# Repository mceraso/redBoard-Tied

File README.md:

# redBoard-Tied
Eagle Project to tie together redundant pins of the Sparkfun Quadstepper Motor Driver Board (the Red Board). When UNO Robotics first used the Red Board,
we realized quickly that we did not need all the pins available on the board. We wanted to save space on our Arduino, so we began to solder connections as pictured below.
After Sparkfun retired the Red Board, we were interested to see that they had left their designs open to the public. We wondered if we could continue making our own Red Boards while iterating on their design.
This project attempted to tie together the pins on the board that we used to solder by hand.

The first prototype failed in spectacular fashion as pictured below. We ordered our Red Board design from MacroFab with 1oz copper while Sparkfun's original design demanded 2oz copper. Because our prototpye had half as much copper as it needed, it could not handle the current, heated up quickly, and caught fire.

UNO Robotics has decided to put this project on hold due to the high cost of 2oz copper board fabrication and because the University of New Orleans has acquired its own PCB fabrication machine. As we improve in-house PCB fabrication ability, we intend to come back to the RedBoard project.

8.29.18: DEVELOPMENT IS BACK ON.
Because of our performance in the 2018 season, UNO Robotics has secured funding to move forward with a prototype of redBoard-Tied with 2oz copper. We're finalzing the parts list and will place an order with MacroFab soon.

# Original Red Board Front: 

# Original Red Board Back:

# How We Used to Tie the Board:

# redBoard-Tied Front:

# redBoard-Tied Back:

# Prototype Front:

# Prototype Back:

# Helpful Links:
Quadstepper from SparkFun: https://www.sparkfun.com/products/retired/10507

Sparkfun's Quadstepper Repository: https://github.com/sparkfun/Quadstepper_Motor_Driver/tree/V_2.0.1

MacroFab: https://macrofab.com/

Eagle Tutorial from SparkFun: https://learn.sparkfun.com/tutorials/how-to-install-and-setup-eagle

UNO Robotics: http://www.uno.edu/student-involvement-leadership/orgs/robotics-club.aspx

GoFundMe: https://www.gofundme.com/unorobotics

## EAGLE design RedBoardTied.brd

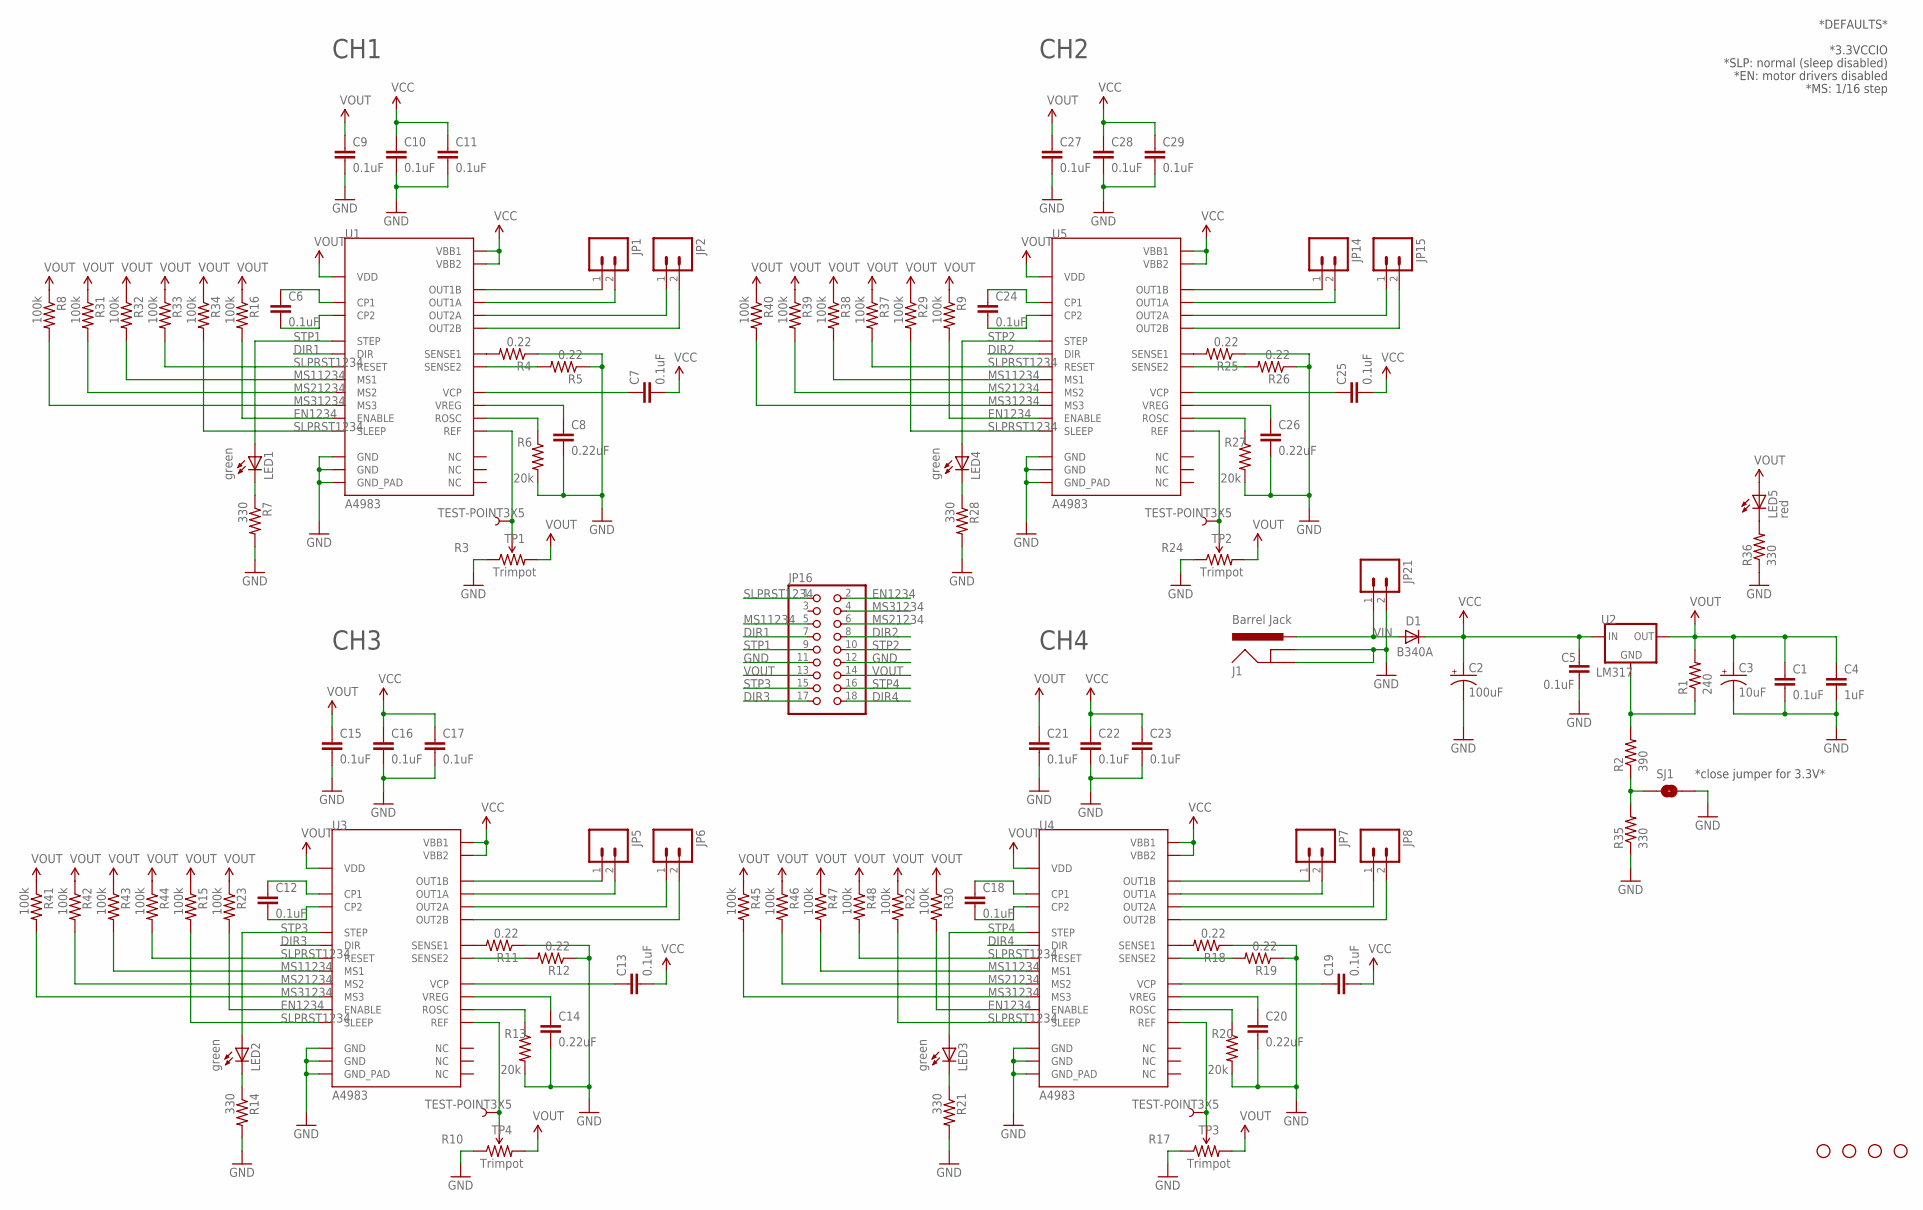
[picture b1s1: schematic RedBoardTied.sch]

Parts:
C1, C5, C6, C7, C9, C10, C11, C12, C13, C15, C16, C17, C18, C19, C21, C22, C23, C24, C25, C27, C28, C29: 0.1uF; 0402-CAP
C2: 100uF; PANASONIC_G
C3: 10uF; EIA3216
C4: 1uF; 0805
C8, C14, C20, C26: 0.22uF; 0402-CAP
D1: B340A; SMA-DIODE
J1: Barrel Jack; POWER_JACK_SMD
JP1, JP2, JP5, JP6, JP7, JP8, JP14, JP15: M023.5MM_LOCK; SCREWTERMINAL-3.5MM-2_LOCK
JP9, JP10, JP11, JP12: STAND-OFF
JP16: PINHD-2X9; 2X09
JP21: M02PTH; 1X02
LED1, LED2, LED3, LED4: green; LED-0603
LED5: red; LED-0603
R1: 240; 0402-RES
R2: 390; 0402-RES
R3, R10, R17, R24: Trimpot; TRIMPOT-3MM
R4, R5, R11, R12, R18, R19, R25, R26: 0.22; 0805
R6, R13, R20, R27: 20k; 0402-RES
R7, R14, R21, R28, R35, R36: 330; 0402-RES
R8, R9, R15, R16, R22, R23, R29, R30, R31, R32, R33, R34, R37, R38, R39, R40, R41, R42, R43, R44, R45, R46, R47, R48: 100k; 0402-RES
SJ1: SOLDERJUMPERNO; SJ_2S-NO
TP1, TP2, TP3, TP4: TEST-POINT3X5; PAD.03X.05
U1, U3, U4, U5: A4983; QFN-28-5MM
U2: LM317; DPAK

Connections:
DIR1: JP16.7, U1.P$19 (DIR)
DIR2: JP16.8, U5.P$19 (DIR)
DIR3: JP16.17, U3.P$19 (DIR)
DIR4: JP16.18, U4.P$19 (DIR)
EN1234: JP16.2, R9.2, R16.2, R23.2, R30.2, U1.P$2 (ENABLE), U3.P$2 (ENABLE), U4.P$2 (ENABLE), U5.P$2 (ENABLE)
GND: C1.2, C2.-, C3.C (-), C4.2, C5.2, C8.2, C9.2, C10.2, C11.2, C14.2, C15.2, C16.2, C17.2, C20.2, C21.2, C22.2, C23.2, C26.2, C27.2, C28.2, C29.2, J1.GND (GNDBREAK), J1.P$4 (GND), JP16.11, JP16.12, JP21.2, R3.1 (CCW), R4.1, R5.1, R6.2, R7.2, R10.1 (CCW), R11.1, R12.1, R13.2, R14.2, R17.1 (CCW), R18.1, R19.1, R20.2, R21.2, R24.1 (CCW), R25.1, R26.1, R27.2, R28.2, R35.1, R36.1, SJ1.2, U1.P$3 (GND), U1.P$18 (GND), U1.P$29 (GND_PAD), U3.P$3 (GND), U3.P$18 (GND), U3.P$29 (GND_PAD), U4.P$3 (GND), U4.P$18 (GND), U4.P$29 (GND_PAD), U5.P$3 (GND), U5.P$18 (GND), U5.P$29 (GND_PAD)
MS11234: JP16.5, R32.2, R38.2, R43.2, R47.2, U1.P$9 (MS1), U3.P$9 (MS1), U4.P$9 (MS1), U5.P$9 (MS1)
MS21234: JP16.6, R31.2, R39.2, R42.2, R46.2, U1.P$10 (MS2), U3.P$10 (MS2), U4.P$10 (MS2), U5.P$10 (MS2)
MS31234: JP16.4, R8.2, R40.2, R41.2, R45.2, U1.P$11 (MS3), U3.P$11 (MS3), U4.P$11 (MS3), U5.P$11 (MS3)
unnamed: R1.1, R2.2, U2.1 (GND)
unnamed: JP1.1, U1.P$21 (OUT1B)
unnamed: JP1.2, U1.P$24 (OUT1A)
unnamed: JP2.1, U1.P$26 (OUT2A)
unnamed: JP2.2, U1.P$1 (OUT2B)
unnamed: R4.2, U1.P$23 (SENSE1)
unnamed: R5.2, U1.P$27 (SENSE2)
unnamed: C7.1, U1.P$6 (VCP)
unnamed: C8.1, U1.P$8 (VREG)
unnamed: R6.1, U1.P$13 (ROSC)
unnamed: C6.1, U1.P$4 (CP1)
unnamed: R3.2 (WIPER), TP1.P$1, U1.P$17 (REF)
unnamed: C6.2, U1.P$5 (CP2)
unnamed: R11.2, U3.P$23 (SENSE1)
unnamed: LED1.C, R7.1
unnamed: R12.2, U3.P$27 (SENSE2)
unnamed: C13.1, U3.P$6 (VCP)
unnamed: C14.1, U3.P$8 (VREG)
unnamed: R13.1, U3.P$13 (ROSC)
unnamed: R10.2 (WIPER), TP4.P$1, U3.P$17 (REF)
unnamed: C12.1, U3.P$4 (CP1)
unnamed: R2.1, R35.2, SJ1.1
unnamed: C12.2, U3.P$5 (CP2)
unnamed: LED2.C, R14.1
unnamed: LED5.C, R36.2
unnamed: JP5.1, U3.P$21 (OUT1B)
unnamed: JP5.2, U3.P$24 (OUT1A)
unnamed: JP6.1, U3.P$26 (OUT2A)
unnamed: JP6.2, U3.P$1 (OUT2B)
unnamed: R18.2, U4.P$23 (SENSE1)
unnamed: R19.2, U4.P$27 (SENSE2)
unnamed: C19.1, U4.P$6 (VCP)
unnamed: C20.1, U4.P$8 (VREG)
unnamed: R20.1, U4.P$13 (ROSC)
unnamed: R17.2 (WIPER), TP3.P$1, U4.P$17 (REF)
unnamed: C18.1, U4.P$4 (CP1)
unnamed: C18.2, U4.P$5 (CP2)
unnamed: LED3.C, R21.1
unnamed: JP7.1, U4.P$21 (OUT1B)
unnamed: JP7.2, U4.P$24 (OUT1A)
unnamed: JP8.1, U4.P$26 (OUT2A)
unnamed: JP8.2, U4.P$1 (OUT2B)
unnamed: R25.2, U5.P$23 (SENSE1)
unnamed: R26.2, U5.P$27 (SENSE2)
unnamed: C25.1, U5.P$6 (VCP)
unnamed: C26.1, U5.P$8 (VREG)
unnamed: R27.1, U5.P$13 (ROSC)
unnamed: R24.2 (WIPER), TP2.P$1, U5.P$17 (REF)
unnamed: C24.1, U5.P$4 (CP1)
unnamed: C24.2, U5.P$5 (CP2)
unnamed: LED4.C, R28.1
unnamed: JP14.1, U5.P$21 (OUT1B)
unnamed: JP14.2, U5.P$24 (OUT1A)
unnamed: JP15.1, U5.P$26 (OUT2A)
unnamed: JP15.2, U5.P$1 (OUT2B)
SLPRST1234: JP16.1, R15.2, R22.2, R29.2, R33.2, R34.2, R37.2, R44.2, R48.2, U1.P$12 (RESET), U1.P$14 (SLEEP), U3.P$12 (RESET), U3.P$14 (SLEEP), U4.P$12 (RESET), U4.P$14 (SLEEP), U5.P$12 (RESET), U5.P$14 (SLEEP)
STP1: JP16.9, LED1.A, U1.P$16 (STEP)
STP2: JP16.10, LED4.A, U5.P$16 (STEP)
STP3: JP16.15, LED2.A, U3.P$16 (STEP)
STP4: JP16.16, LED3.A, U4.P$16 (STEP)
VCC: C2.+, C5.1, C7.2, C10.1, C11.1, C13.2, C16.1, C17.1, C19.2, C22.1, C23.1, C25.2, C28.1, C29.1, D1.C, U1.P$22 (VBB1), U1.P$28 (VBB2), U2.3 (IN), U3.P$22 (VBB1), U3.P$28 (VBB2), U4.P$22 (VBB1), U4.P$28 (VBB2), U5.P$22 (VBB1), U5.P$28 (VBB2)
VIN: D1.A, J1.VIN0 (PWR), JP21.1
VOUT: C1.1, C3.A (+), C4.1, C9.1, C15.1, C21.1, C27.1, JP16.13, JP16.14, LED5.A, R1.2, R3.3 (CW), R8.1, R9.1, R10.3 (CW), R15.1, R16.1, R17.3 (CW), R22.1, R23.1, R24.3 (CW), R29.1, R30.1, R31.1, R32.1, R33.1, R34.1, R37.1, R38.1, R39.1, R40.1, R41.1, R42.1, R43.1, R44.1, R45.1, R46.1, R47.1, R48.1, U1.P$15 (VDD), U2.4 (OUT), U3.P$15 (VDD), U4.P$15 (VDD), U5.P$15 (VDD)

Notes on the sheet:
CH1
CH2
CH3
CH4
*DEFAULTS*
*MS: 1/16 step
*3.3VCCIO
*close jumper for 3.3V*
*EN: motor drivers disabled
*SLP: normal (sleep disabled)

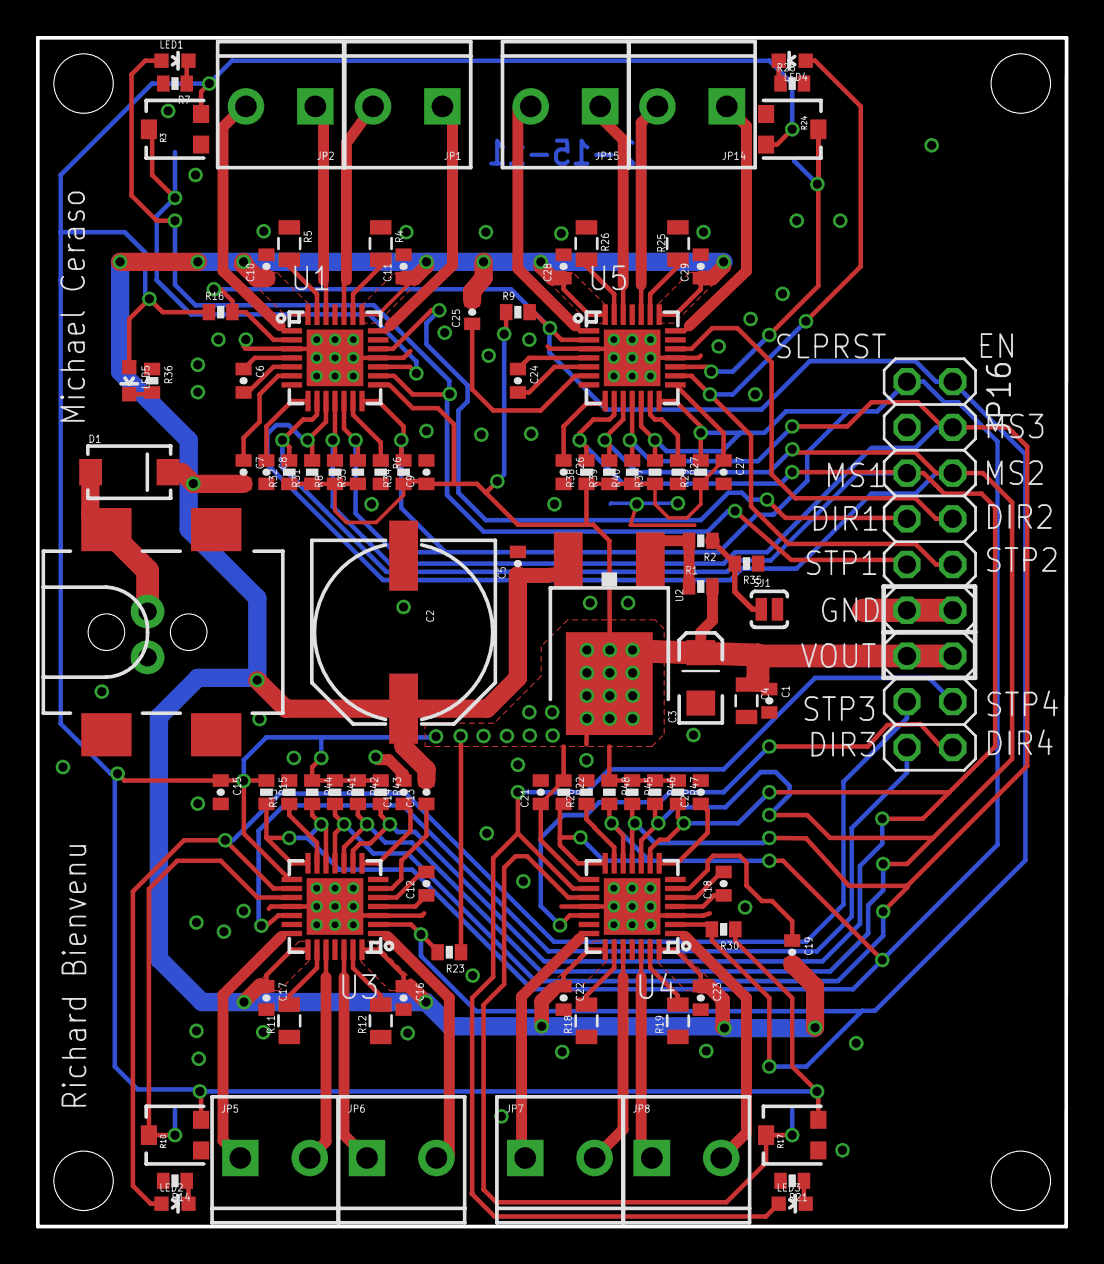
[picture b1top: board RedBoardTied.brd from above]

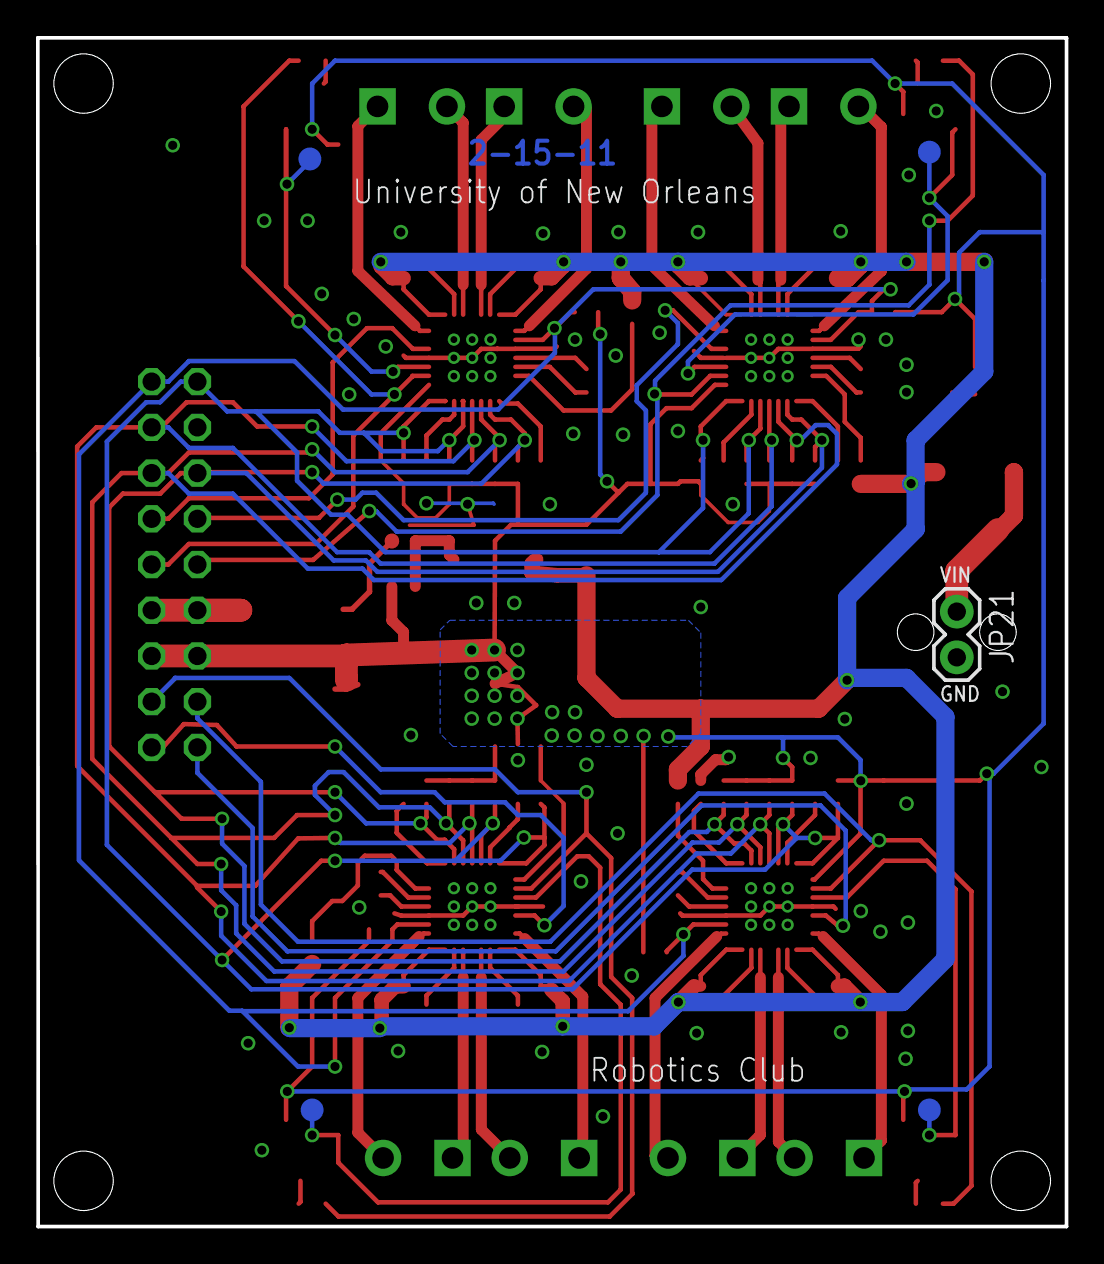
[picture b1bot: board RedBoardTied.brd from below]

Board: 2 copper layers, 57.1 x 66.0 mm, 108 parts (5 on the bottom side), 72 nets.

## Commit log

2017-12-05 .sch and .brd manufactured by MacroFab
